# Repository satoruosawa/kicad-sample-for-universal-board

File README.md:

# kicad-sample-for-universal-board

### ファイルの追加
- Create new project

### 回路図の編集
- Schematic layout editorアイコンをクリックして開始する。
- 部品のレイアウト
  - 部品は標準ライブラリの"device"から選択できる。
  - グランドは Place power port -> power -> GND などを使う。
  - 名前を編集する。名前部分をダブルクリックで編集可能。抵抗やキャパシタ等は定数を記載。
- アノテーション
  - Annotate Schematic Symbols -> Annotateをクリック
- 回路チェック
  - Perform electrical rule checkをクリック
  - 電源系とグランドは電源フラグと接続する。
  - 繋がない端子はPlace no connection flagをつける。
  - For ERC(Electrical rule check)などとして追記する。
- ページ設定
  - Page settingsアイコンをクリック
  - タイトル、日付、リビジョン、所属などを追記
- 出力
  - File -> plot から出力
- netlist の生成
  - generate netlistアイコンをクリックして生成

### フットプリントの作成
自作 or 外部ライブラリを使うときは、mylibフォルダに追加する。
- mylib.prettyフォルダを追加する。
- Footprint Editor を開いて、Preferences -> Manage Footprint Libraries... -> Project Specific Librariesタブを開く。
- Browse Librariesをクリックして、mylib.prettyフォルダを追加する。kicadからmylibが参照可能になる。
- フットプリントの編集
  - ユニバーサル基板のピッチは100mil(2.54mm)であることを考慮して設計する。

### コンポーネントとフットプリントの割当て
- Schematic layout editor画面で、Tools -> Assign Footprints... をクリック
- 各コンポーネントにフットプリントを割り当てる。
- View Footprintをクリックすると、フットプリントを確認できる。
- いくつかのフットプリントはデフォルトライブラリに含まれている。
  - Resistor_THT: 一般的な抵抗THT(Through-hole technology)水平、垂直配置、穴の距離など選択可能。秋月の1/4W抵抗はL6.3mm, D2.5mmである。
  - LED_THT: 一般的なLED
  -

### パターンの作図
- PCB layout editorアイコンをクリック
- Page settignsを編集
  - タイトル、日付、リビジョン、所属などを追記
- Setup -> layer setup をクリック
  - 必要なレイヤのみを表示
  - F.Cu	両面基板の場合、おもてのはんだ面になる。被覆のあるワイヤはここが経路になる。
  - B.Cu	はんだづけする面。ワイヤのはんだ付けはここで行う。
  - F.SlkS	部品実装側のシルク印刷面。
  - B.SlkS	はんだ面側のシルク印刷面。
  - Edge.Cuts  基板の外形線を引くレイヤ。
- Setup -> Default Pad propertiesをクリック
  - 使用するユニバーサル基板の寸法に合わせる。ここでは、Hole size を0.9mm, パッドサイズを1.4mmとしておく。
- Setup -> design ruleをクリック
  - Track Widthを0.254とする。
- 実際の配置
  - 外周はEdge.Cutsレイヤーに描画
  - read netlistでnetlistを読み込み
  - 右クリック -> gridから100milを選択すると、するーホールを同じピッチになる。
  - ピンヘッダなどの回路図にないパーツなども追加できる。ピンヘッダはトラ技のデータベースのものが使える。

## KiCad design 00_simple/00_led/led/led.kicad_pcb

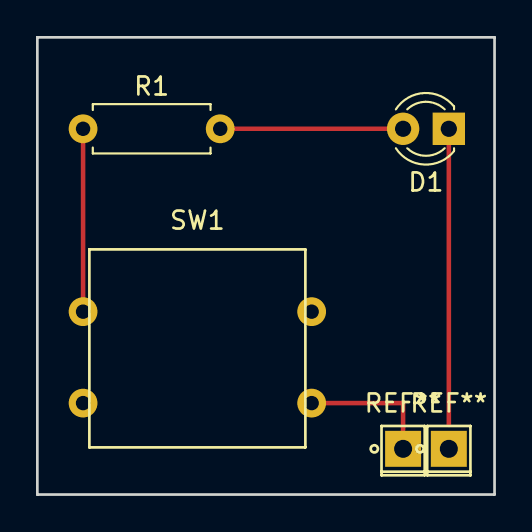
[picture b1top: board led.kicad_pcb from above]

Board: 2 copper layers, 25.4 x 25.4 mm, 3 parts (0 on the bottom side), 2 nets.

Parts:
D1: OSR5JA3Z74A; LED_D3.0mm
R1: 640; R_Axial_DIN0207_L6.3mm_D2.5mm_P7.62mm_Horizontal
SW1: SW_SPST; TVGP01-G73BB

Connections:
unnamed: D1.2, R1.2
unnamed: R1.1, SW1.1

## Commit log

2018-08-30 add gitignore
2018-08-30 create new project
2018-08-30 draw schematic
2018-08-30 add annotation
2018-08-30 add ERC
2018-08-30 page settings
2018-08-30 plot
2018-08-30 generate netlist
2018-08-30 add mylib.pretty
2018-08-30 add switch
2018-08-30 assign footprints
2018-08-30 add PCB
2018-08-30 change layer setup
2018-08-30 change pad properties
2018-08-30 draw edge
2018-08-30 set parts
2018-08-30 add pinheader
2018-09-11 add libraries
2018-09-11 add 01_inverting_operational_amplifier
2018-09-11 add 02_non_inverting_operational_amplifier
2018-09-11 add pdfs
2018-09-12 change circuit
2018-09-12 change pdf
2018-09-13 add npn
2018-09-13 add pdf
2018-09-13 add pnp
2018-09-13 add nmos fet
2018-09-15 update 03
2018-09-15 update 04
2018-09-15 update 05
2018-09-15 add 06
2018-09-15 rename
2018-09-15 add07
2018-09-15 bug fix
2018-09-15 add pnp2
2018-09-15 add power LED
